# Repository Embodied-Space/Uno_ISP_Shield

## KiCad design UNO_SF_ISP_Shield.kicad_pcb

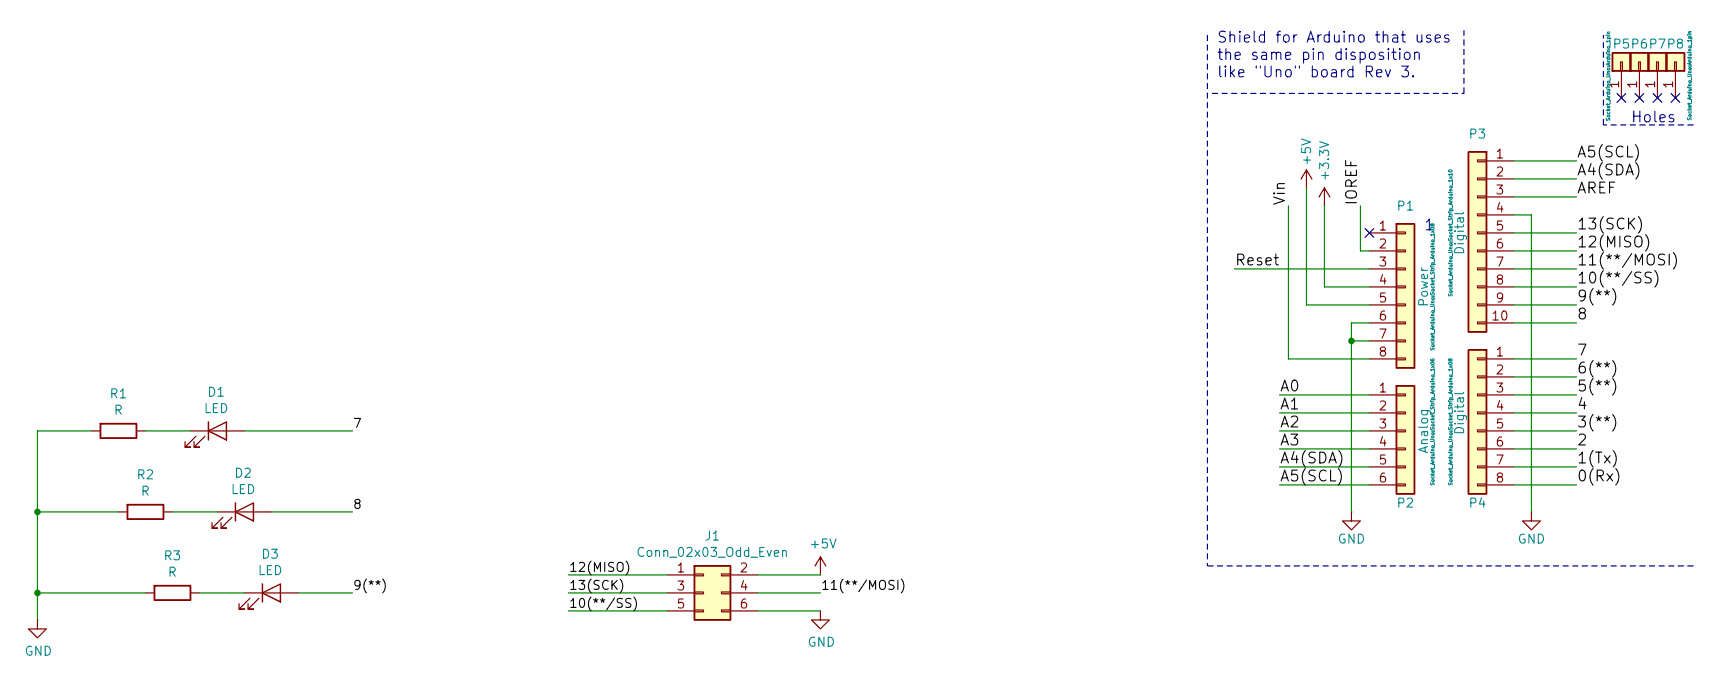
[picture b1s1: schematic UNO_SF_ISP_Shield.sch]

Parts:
D1, D2, D3: LED; LED_D3.0mm_FlatTop
J1: Conn_02x03_Odd_Even; PinHeader_2x03_P2.54mm_Vertical
P1: Power; Socket_Strip_Arduino_1x08
P2: Analog; Socket_Strip_Arduino_1x06
P3: Digital; Socket_Strip_Arduino_1x10
P4: Digital; Socket_Strip_Arduino_1x08
P5, P6, P7, P8: CONN_01X01; Arduino_1pin
R1, R2, R3: R; R_Axial_DIN0309_L9.0mm_D3.2mm_P15.24mm_Horizontal

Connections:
+3V3: P1.4
+5V: J1.2, P1.5
/0(Rx): P4.8
/1(Tx): P4.7
/2: P4.6
/3(**): P4.5
/4: P4.4
/5(**): P4.3
/6(**): P4.2
/7: D1.2 (A), P4.1
/8: D2.2 (A), P3.10
/9(**): D3.2 (A), P3.9
/10(**/SS): J1.5, P3.8
/11(**/MOSI): J1.4, P3.7
/12(MISO): J1.1, P3.6
/13(SCK): J1.3, P3.5
/A0: P2.1
/A1: P2.2
/A2: P2.3
/A3: P2.4
/A4(SDA): P2.5, P3.2
/A5(SCL): P2.6, P3.1
/AREF: P3.3
/IOREF: P1.2
/Reset: P1.3
/Vin: P1.8
GND: J1.6, P1.6, P1.7, P3.4, R1.2, R2.2, R3.2
unnamed: D1.1 (K), R1.1
unnamed: D2.1 (K), R2.1
unnamed: D3.1 (K), R3.1

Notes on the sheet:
Holes
Shield for Arduino that uses the same pin disposition like "Uno" board Rev 3.

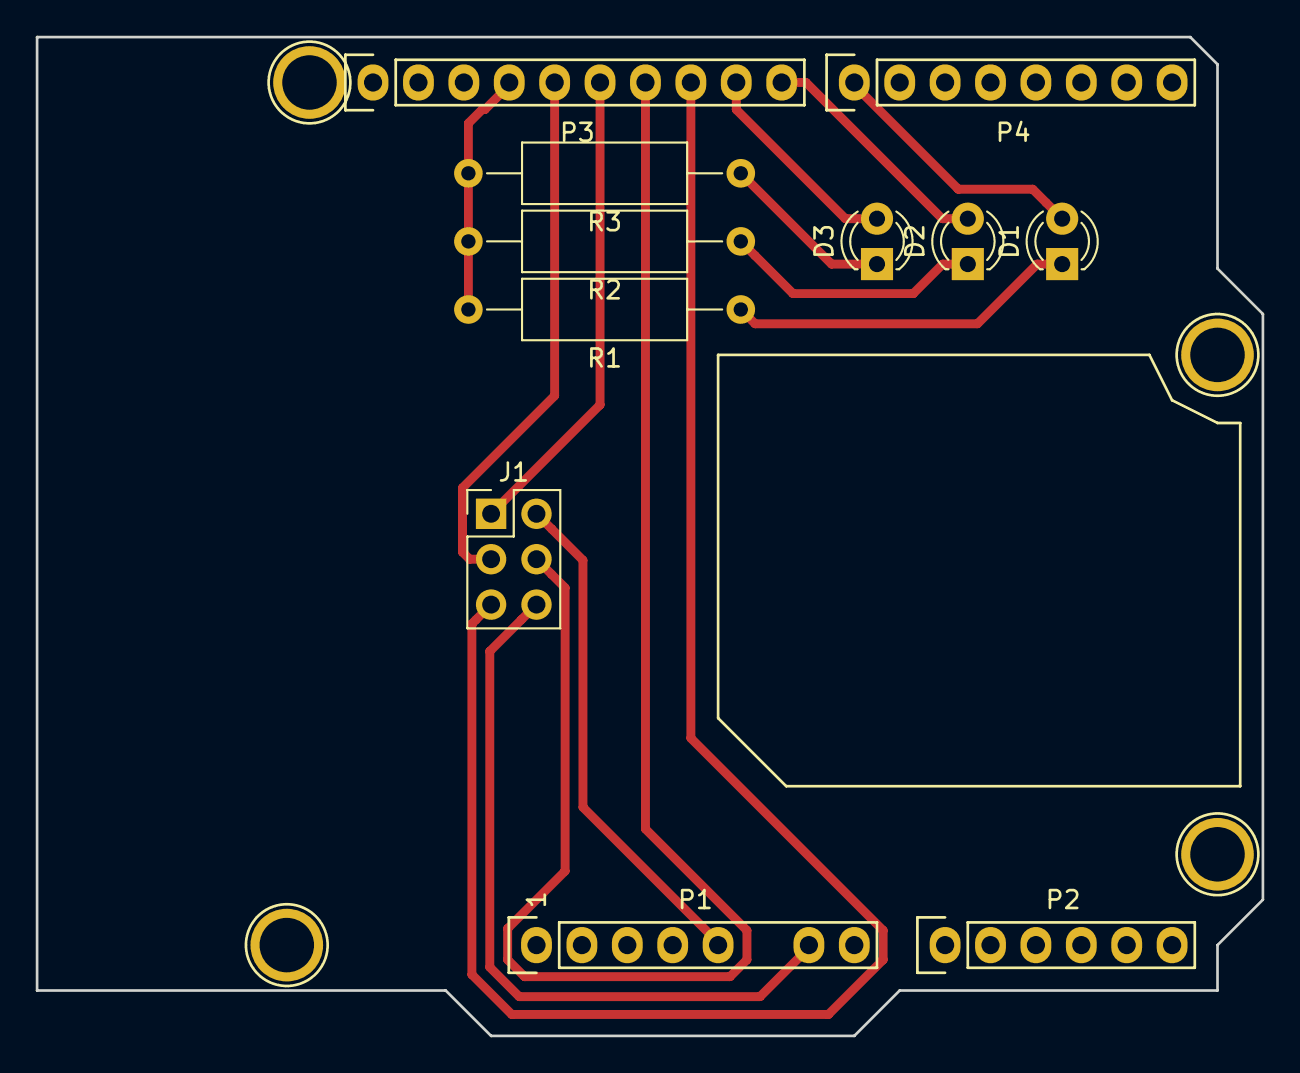
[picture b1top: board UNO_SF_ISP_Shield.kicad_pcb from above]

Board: 2 copper layers, 68.6 x 55.9 mm, 15 parts (0 on the bottom side), 14 nets.

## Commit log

2020-11-14 first layout
